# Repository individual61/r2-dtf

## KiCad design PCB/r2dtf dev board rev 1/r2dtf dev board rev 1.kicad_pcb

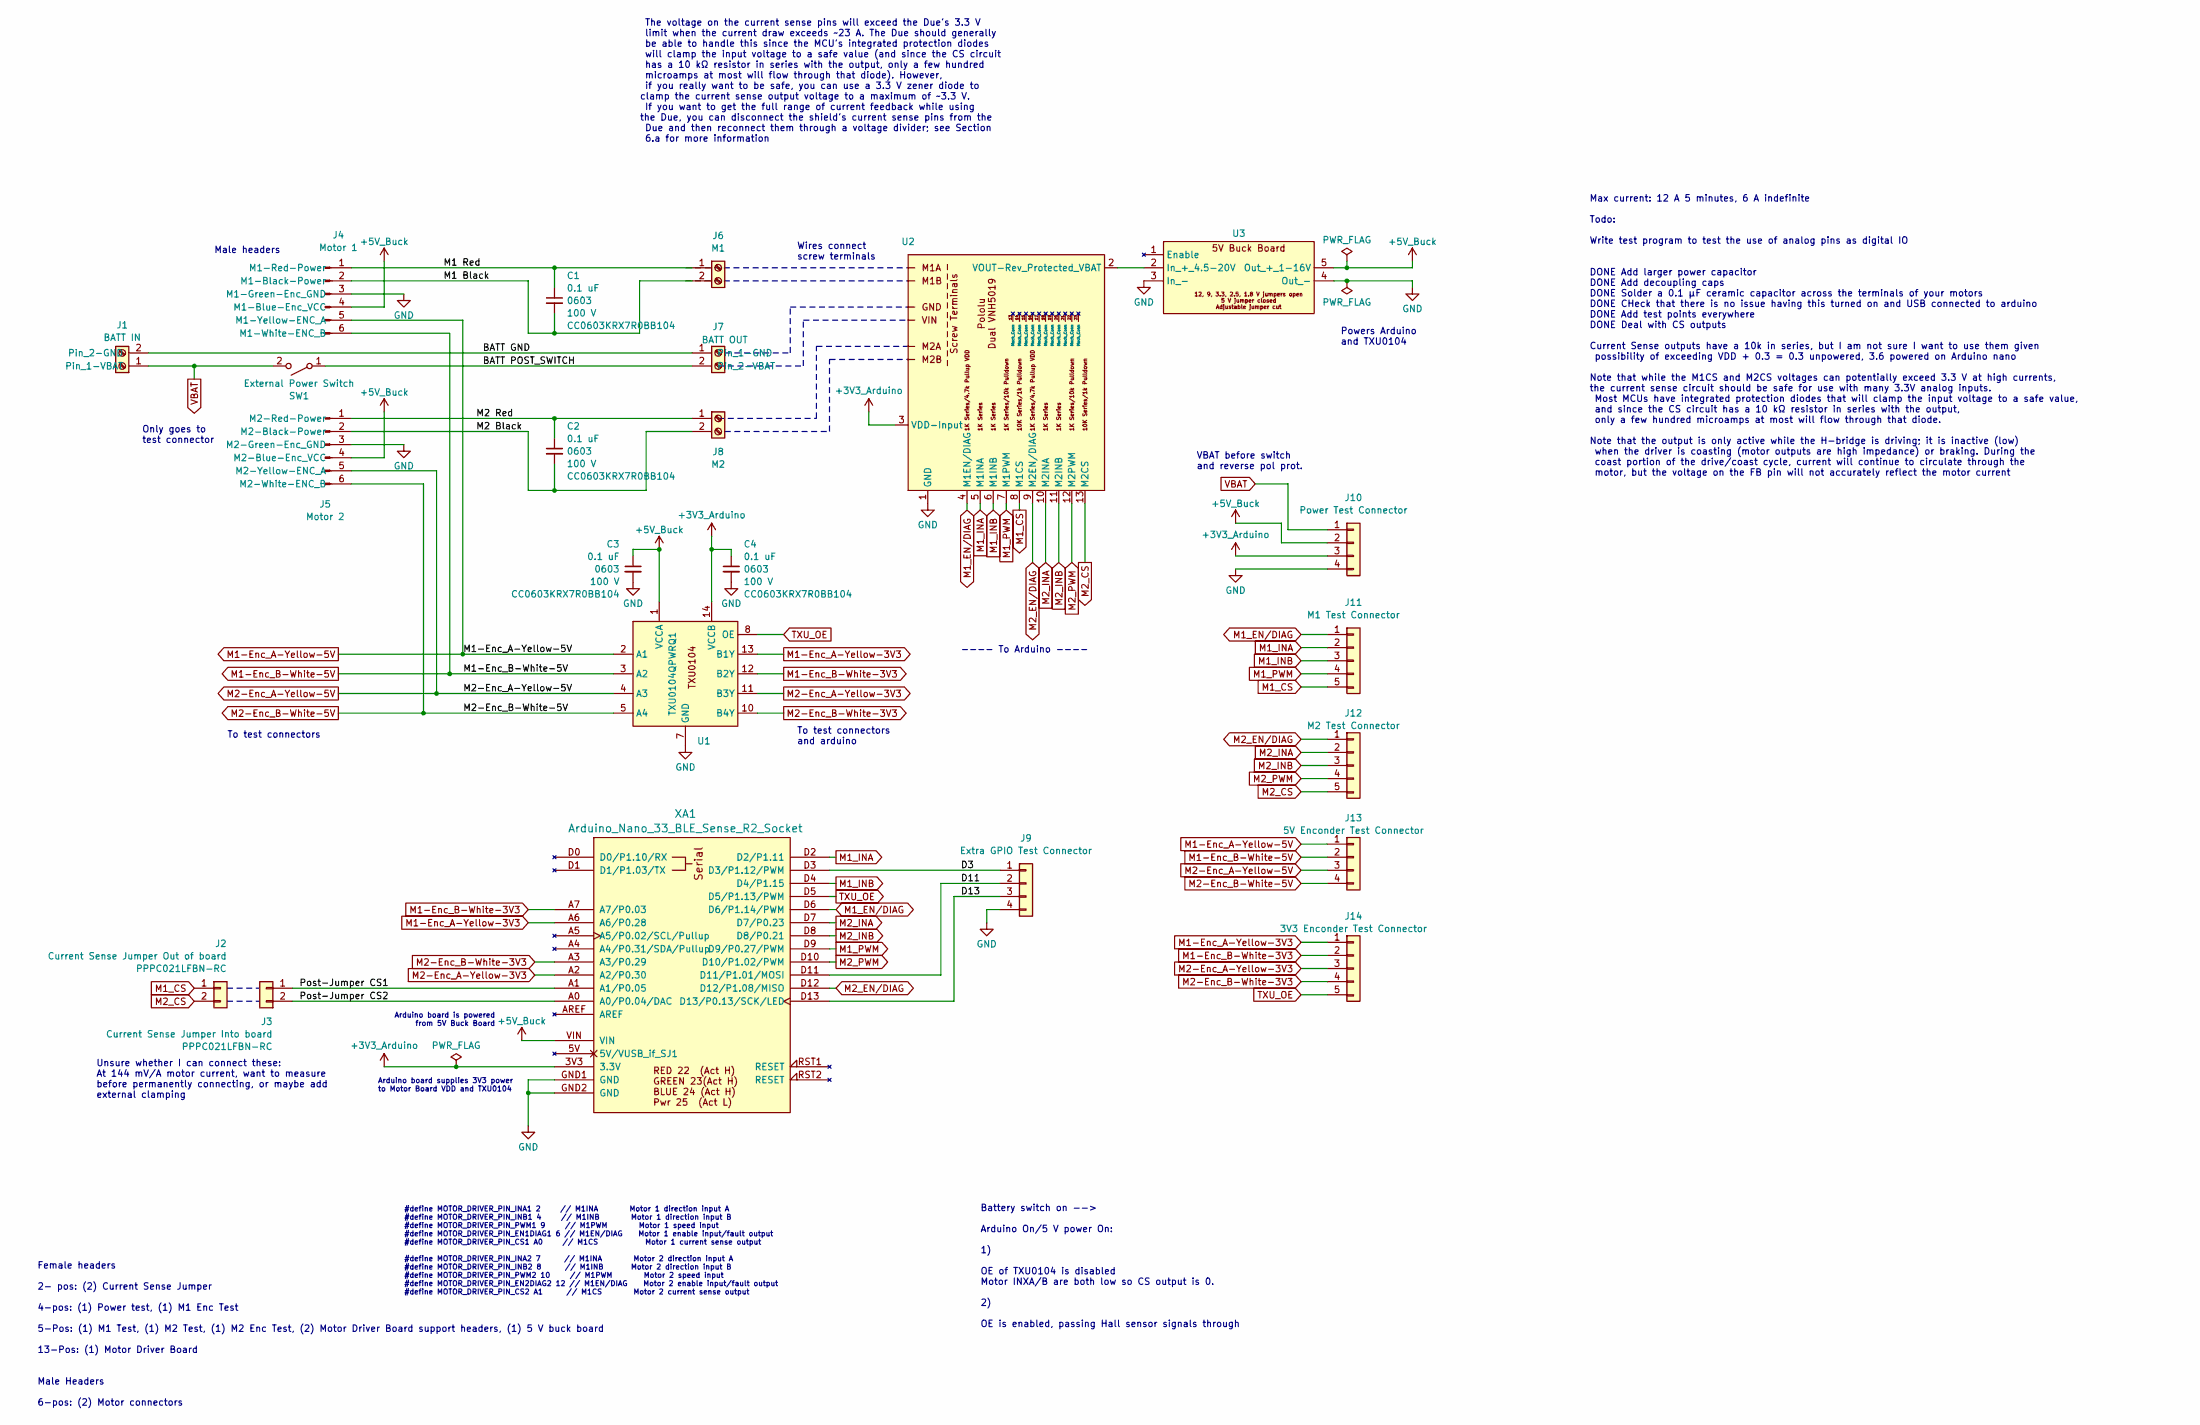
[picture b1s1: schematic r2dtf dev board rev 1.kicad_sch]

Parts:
C1, C2, C3, C4: 0.1 uF; C_0603_1608Metric_Pad1.08x0.95mm_HandSolder; Voltage Rating 100 V; MPN CC0603KRX7R0BB104; Digi-Key_PN 311-1523-1-ND
J1: BATT IN; Screw Terminal 2P 5 mm, Degson DG301-5.0-02P
J2: Current Sense Jumper Out of board; Sullins Header Female TH 2 x 1 PPPC021LFBN-RC; MPN PPPC021LFBN-RC
J3: Current Sense Jumper Into board; Sullins Header Female TH 2 x 1 PPPC021LFBN-RC; MPN PPPC021LFBN-RC
J4: Motor 1; PinHeader_1x06_P2.54mm_Vertical
J5: Motor 2; PinHeader_1x06_P2.54mm_Vertical
J6: M1; Screw Terminal 2P 5 mm, Degson DG301-5.0-02P
J7: BATT OUT; Screw Terminal 2P 5 mm, Degson DG301-5.0-02P
J8: M2; Screw Terminal 2P 5 mm, Degson DG301-5.0-02P
J9: Extra GPIO Test Connector; Sullins Header Female TH 4 x 1 PPPC041LFBN-RC; MPN PPPC041LFBN-RC
J10: Power Test Connector; Sullins Header Female TH 4 x 1 PPPC041LFBN-RC; MPN PPPC041LFBN-RC
J11: M1 Test Connector; Sullins Header Female TH 5 x 1 PPPC051LFBN-RC; MPN PPPC051LFBN-RC
J12: M2 Test Connector; Sullins Header Female TH 5 x 1 PPPC051LFBN-RC; MPN PPPC051LFBN-RC
J13: 5V Enconder Test Connector; Sullins Header Female TH 4 x 1 PPPC041LFBN-RC; MPN PPPC041LFBN-RC
J14: 3V3 Enconder Test Connector; Sullins Header Female TH 5 x 1 PPPC051LFBN-RC; MPN PPPC051LFBN-RC
SW1: External Power Switch; Daier MTS-101 Toggle Switch 6A 125 VAC
U1: TSSOP-14_4.4x5mm_P0.65mm; MPN TXU0104QPWRQ1
U2: Pololu Dual VNH5019 Motor Driver rev ash02b
U3: 12V to 5V Buck Converter; Drok 5 V Buck Converter
XA1: Arduino_Nano_33_BLE_Sense_R2_Socket; Arduino_Nano_Every_Socket

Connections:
+3V3: C4.1, J10.3, U1.14 (VCCB), U2.3 (VDD-Input), XA1.3V3 (3.3V)
+5V: C3.1, J4.4 (M1-Blue-Enc_VCC), J5.4 (M2-Blue-Enc_VCC), J10.2, U1.1 (VCCA), U3.5 (Out_+_1-16V), XA1.VIN
/BATT GND: J1.2 (Pin_2-GND), J7.1 (Pin_1-GND)
/BATT POST_SWITCH: J7.2 (Pin_2-VBAT), SW1.1 (A)
/D3: J9.1, XA1.D3 (D3/P1.12/PWM)
/D11: J9.2, XA1.D11 (D11/P1.01/MOSI)
/D13: J9.3, XA1.D13 (D13/P0.13/SCK/LED)
/M1 Black: C1.2, J4.2 (M1-Black-Power), J6.2
/M1 Red: C1.1, J4.1 (M1-Red-Power), J6.1
/M2 Black: C2.2, J5.2 (M2-Black-Power), J8.2
/M2 Red: C2.1, J5.1 (M2-Red-Power), J8.1
/Post-Jumper CS1: J3.1, XA1.A1 (A1/P0.05)
/Post-Jumper CS2: J3.2, XA1.A0 (A0/P0.04/DAC)
GND: C3.2, C4.2, J4.3 (M1-Green-Enc_GND), J5.3 (M2-Green-Enc_GND), J9.4, J10.4, U1.7 (GND), U2.1 (GND), U3.3 (In_-), U3.4 (Out_-), XA1.GND1 (GND), XA1.GND2 (GND)
M1-Enc_A-Yellow-3V3: J14.1, U1.13 (B1Y), XA1.A6 (A6/P0.28)
M1-Enc_A-Yellow-5V: J4.5 (M1-Yellow-ENC_A), J13.1, U1.2 (A1)
M1-Enc_B-White-3V3: J14.2, U1.12 (B2Y), XA1.A7 (A7/P0.03)
M1-Enc_B-White-5V: J4.6 (M1-White-ENC_B), J13.2, U1.3 (A2)
M1_CS: J2.1, J11.5, U2.8 (M1CS)
M1_EN/DIAG: J11.1, U2.4 (M1EN/DIAG), XA1.D6 (D6/P1.14/PWM)
M1_INA: J11.2, U2.5 (M1INA), XA1.D2 (D2/P1.11)
M1_INB: J11.3, U2.6 (M1INB), XA1.D4 (D4/P1.15)
M1_PWM: J11.4, U2.7 (M1PWM), XA1.D9 (D9/P0.27/PWM)
M2-Enc_A-Yellow-3V3: J14.3, U1.11 (B3Y), XA1.A2 (A2/P0.30)
M2-Enc_A-Yellow-5V: J5.5 (M2-Yellow-ENC_A), J13.3, U1.4 (A3)
M2-Enc_B-White-3V3: J14.4, U1.10 (B4Y), XA1.A3 (A3/P0.29)
M2-Enc_B-White-5V: J5.6 (M2-White-ENC_B), J13.4, U1.5 (A4)
M2_CS: J2.2, J12.5, U2.13 (M2CS)
M2_EN/DIAG: J12.1, U2.9 (M2EN/DIAG), XA1.D12 (D12/P1.08/MISO)
M2_INA: J12.2, U2.10 (M2INA), XA1.D7 (D7/P0.23)
M2_INB: J12.3, U2.11 (M2INB), XA1.D8 (D8/P0.21)
M2_PWM: J12.4, U2.12 (M2PWM), XA1.D10 (D10/P1.02/PWM)
unnamed: U2.2 (VOUT-Rev_Protected_VBAT), U3.2 (In_+_4.5-20V)
TXU_OE: J14.5, U1.8 (OE), XA1.D5 (D5/P1.13/PWM)
VBAT: J1.1 (Pin_1-VBAT), J10.1, SW1.2 (B)

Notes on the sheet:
---- To Arduino ----
To test connectors
The voltage on the current sense pins will exceed the Due's 3.3 V limit when the current draw exceeds ~23 A. The Due should generally be able to handle this since the MCU's integrated protection diodes will clamp the input voltage to a safe value (and since the CS circuit has a 10 kΩ resistor in se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
To test connectors and arduino
Arduino board supplies 3V3 power to Motor Board VDD and TXU0104
VBAT before switch and reverse pol prot.
Battery switch on --> Arduino On/5 V power On: 1) OE of TXU0104 is disabled Motor INXA/B are both low so CS output is 0. 2) OE is enabled, passing Hall sensor signals through
#define MOTOR_DRIVER_PIN_INA1 2 // M1INA Motor 1 direction input A #define MOTOR_DRIVER_PIN_INB1 4 // M1INB Motor 1 direction input B #define MOTOR_DRIVER_PIN_PWM1 9 // M1PWM Motor 1 speed input #define MOTOR_DRIVER_PIN_EN1DIAG1 6 // M1EN/DIAG Motor 1 enable input/fault output #define MOTOR_DRIVER_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
Powers Arduino and TXU0104
Unsure whether I can connect these: At 144 mV/A motor current, want to measure before permanently connecting, or maybe add external clamping
Female headers 2- pos: (2) Current Sense Jumper 4-pos: (1) Power test, (1) M1 Enc Test 5-Pos: (1) M1 Test, (1) M2 Test, (1) M2 Enc Test, (2) Motor Driver Board support headers, (1) 5 V buck board 13-Pos: (1) Motor Driver Board Male Headers 6-pos: (2) Motor connectors
Male headers
Arduino board is powered from 5V Buck Board
Only goes to test connector
Wires connect screw terminals
Max current: 12 A 5 minutes, 6 A indefinite Todo: Write test program to test the use of analog pins as digital IO DONE Add larger power capacitor DONE Add decoupling caps DONE Solder a 0.1 µF ceramic capacitor across the terminals of your motors DONE CHeck that there is no issue having this turned 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

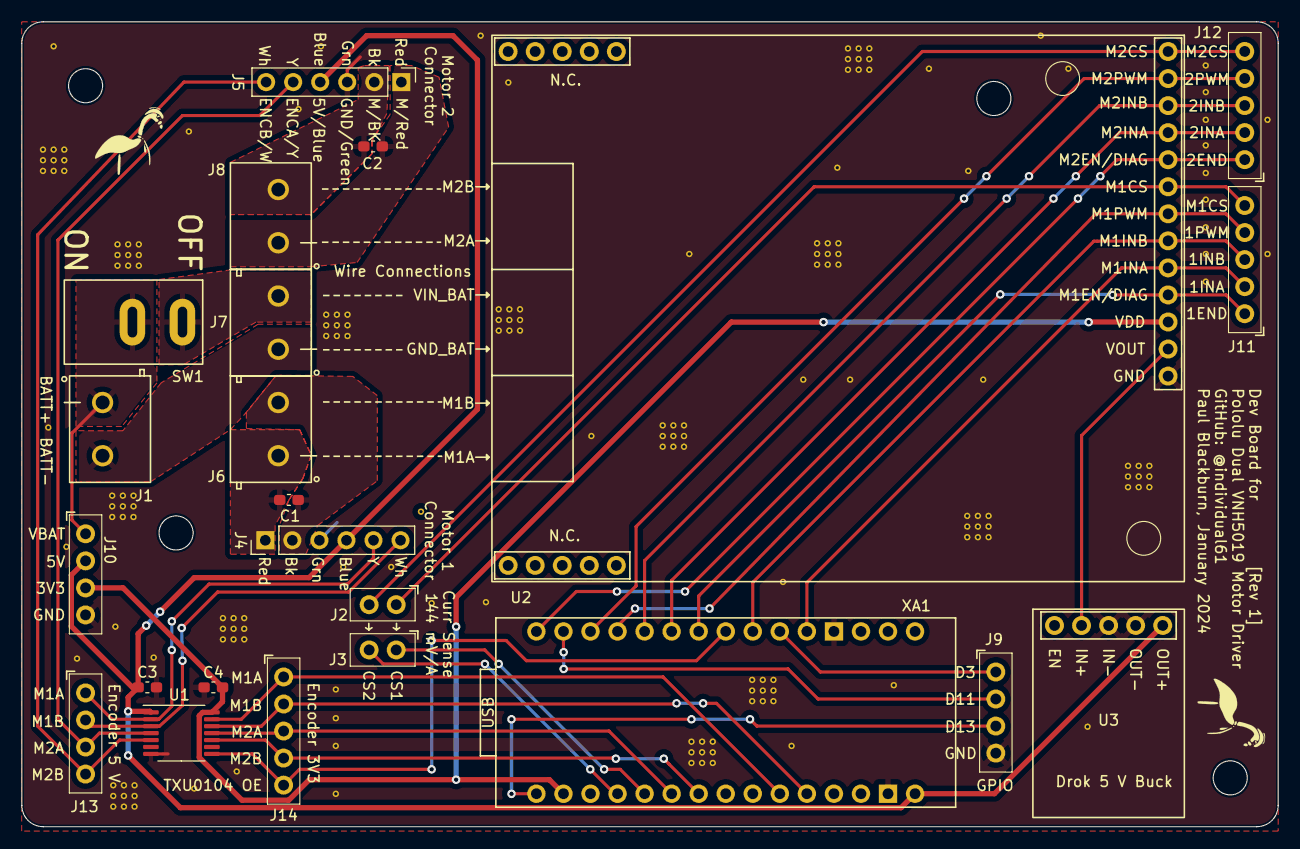
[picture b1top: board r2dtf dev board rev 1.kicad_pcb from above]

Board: 2 copper layers, 118.0 x 75.6 mm, 23 parts (0 on the bottom side), 35 nets.

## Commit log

2018-06-30 Got blink and Serial over USB running
2020-09-20 Tidying up
2024-01-12 Initial work done on dev board and first code test
2024-01-14 Moved from library to my own motor functions, first working test of fast PWM
2024-01-15 Added Test Connectors, connected Arduino, rearranged
2024-01-17 Completed schematic, footprints, initial ratsnest layout of board
2024-01-19 First pass at complete Rev 1. About to quote with JLCPCB
2024-01-19 Removed thermal reliefs on high current pours
2024-01-23 Qt Gui - sucessful serial comms bidirectional
2024-01-26 Successful binary comms from arduino to Qt
2024-01-30 Most read and write of GUI done, some bits and pieces to polish
    Like brake, drive, etc.
2024-01-30 Not sure if anything changed but first successful test through to motor turning!
2024-02-02 Before moving to a two-message sending method
    serial seems to choke if sending more than 128 bytes.
2024-02-06 Most bugs fixed, working as intended
    Still have to implement IMU
2024-02-15 First successful use of an imu fusion library
    After getting total assblast from the three Adafruit_AHRS algorithms, https://github.com/xioTechnologies/Fusion finally produces something I can work with.
2024-02-16 Got a basic Processing visualizer going
2024-02-22 Report more Fusion library parameters
2024-02-22 Able to set Fusion algo parameters via < > command
2024-02-24 Beginning to make a new structure because I can't get the Fusion filter to behave and so I'm going to yolo it with PID
2024-02-27 Built and printed the Rev 1 frame
2025-01-21 Found some changes since last commit
